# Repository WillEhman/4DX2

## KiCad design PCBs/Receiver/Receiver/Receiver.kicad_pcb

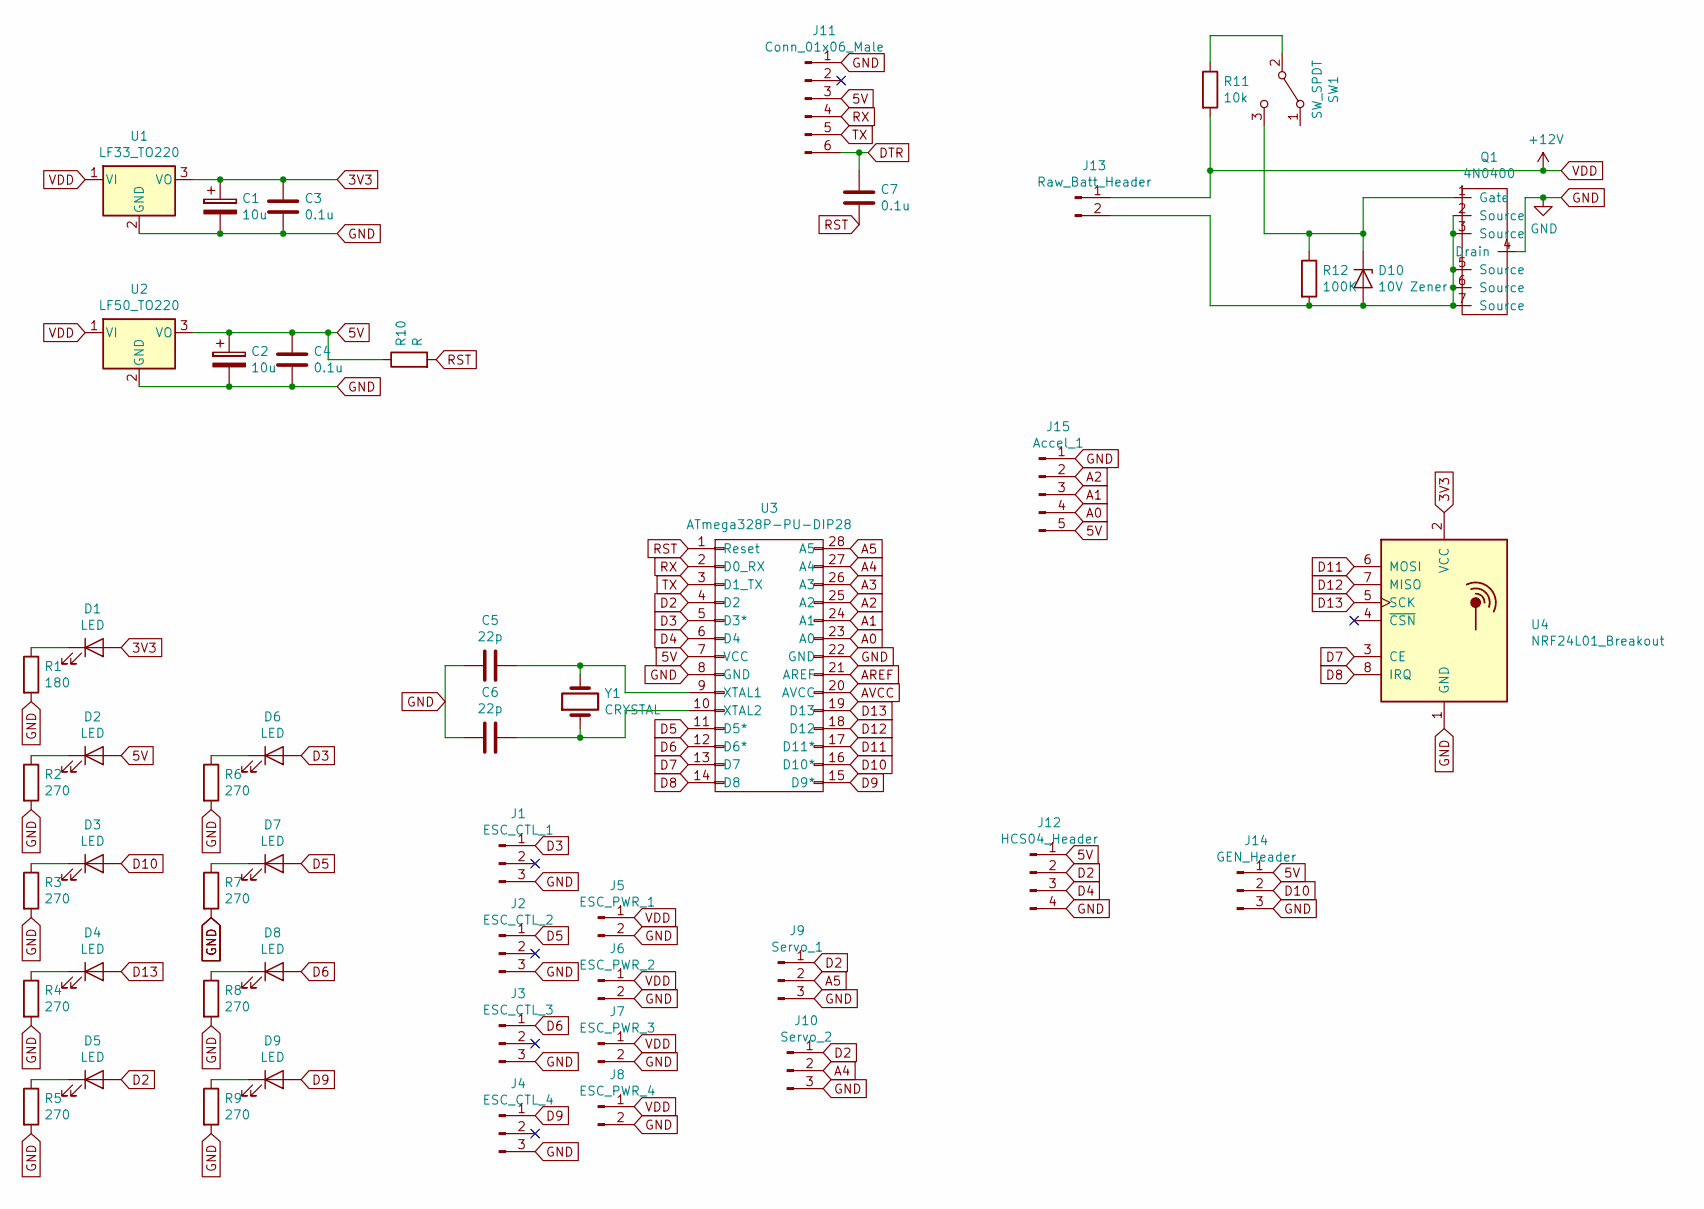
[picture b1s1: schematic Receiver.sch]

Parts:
C1, C2: 10u; CP_Radial_D5.0mm_P2.00mm
C3, C4, C7: 0.1u; C_Axial_L5.1mm_D3.1mm_P7.50mm_Horizontal
C5, C6: 22p; C_Axial_L3.8mm_D2.6mm_P7.50mm_Horizontal
D1, D2, D3, D4, D5, D6, D7, D8, D9: LED; LED_D3.0mm
D10: 10V Zener; D_DO-35_SOD27_P7.62mm_Horizontal
J1: ESC_CTL_1; PinHeader_1x03_P2.54mm_Horizontal
J2: ESC_CTL_2; PinHeader_1x03_P2.54mm_Horizontal
J3: ESC_CTL_3; PinHeader_1x03_P2.54mm_Horizontal
J4: ESC_CTL_4; PinHeader_1x03_P2.54mm_Horizontal
J5: ESC_PWR_1; SolderWirePad_1x02_P7.62mm_Drill2.5mm
J6: ESC_PWR_2; SolderWirePad_1x02_P7.62mm_Drill2.5mm
J7: ESC_PWR_3; SolderWirePad_1x02_P7.62mm_Drill2.5mm
J8: ESC_PWR_4; SolderWirePad_1x02_P7.62mm_Drill2.5mm
J9: Servo_1; PinHeader_1x03_P2.54mm_Vertical
J10: Servo_2; PinHeader_1x03_P2.54mm_Vertical
J11: Conn_01x06_Male; PinHeader_1x06_P2.54mm_Vertical
J12: HCS04_Header; PinSocket_1x04_P2.54mm_Vertical
J13: Raw_Batt_Header; SolderWirePad_1x02_P7.62mm_Drill2.5mm
J14: GEN_Header; PinSocket_1x03_P2.54mm_Vertical
J15: Accel_1; PinSocket_1x05_P2.54mm_Vertical
Q1: 4N0400; TO-263-7_TabPin4
R1: 180; R_Axial_DIN0207_L6.3mm_D2.5mm_P10.16mm_Horizontal
R2, R3, R4, R5, R6, R7, R8, R9: 270; R_Axial_DIN0207_L6.3mm_D2.5mm_P10.16mm_Horizontal
R10: R; R_Axial_DIN0207_L6.3mm_D2.5mm_P10.16mm_Horizontal
R11: 10k; R_Axial_DIN0207_L6.3mm_D2.5mm_P10.16mm_Horizontal
R12: 100K; R_Axial_DIN0207_L6.3mm_D2.5mm_P10.16mm_Horizontal
SW1: SW_SPDT; PinSocket_1x03_P2.54mm_Vertical
U1: LF33_TO220; TO-220-3_Vertical
U2: LF50_TO220; TO-220-3_Vertical
U3: ATmega328P-PU-DIP28; DIP-28_W7.62mm_Socket
U4: NRF24L01_Breakout; nRF24L01_Breakout
Y1: CRYSTAL; Crystal_HC49-U_Vertical

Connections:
3V3: C1.1, C3.1, D1.2 (A), U1.3 (VO), U4.2 (VCC)
5V: C2.1, C4.1, D2.2 (A), J11.3, J12.1, J14.1, J15.5, R10.1, U2.3 (VO), U3.7 (VCC)
A0: J15.4, U3.23 (A0)
A1: J15.3, U3.24 (A1)
A2: J15.2, U3.25 (A2)
A3: U3.26 (A3)
A4: J10.2, U3.27 (A4)
A5: J9.2, U3.28 (A5)
AREF: U3.21 (AREF)
AVCC: U3.20 (AVCC)
D2: D5.2 (A), J9.1, J10.1, J12.2, U3.4 (D2)
D3: D6.2 (A), J1.1, U3.5 (D3*)
D4: J12.3, U3.6 (D4)
D5: D7.2 (A), J2.1, U3.11 (D5*)
D6: D8.2 (A), J3.1, U3.12 (D6*)
D7: U3.13 (D7), U4.3 (CE)
D8: U3.14 (D8), U4.8 (IRQ)
D9: D9.2 (A), J4.1, U3.15 (D9*)
D10: D3.2 (A), J14.2, U3.16 (D10*)
D11: U3.17 (D11*), U4.6 (MOSI)
D12: U3.18 (D12), U4.7 (MISO)
D13: D4.2 (A), U3.19 (D13), U4.5 (SCK)
DTR: C7.1, J11.6
GND: C1.2, C2.2, C3.2, C4.2, C5.1, C6.1, J1.3, J2.3, J3.3, J4.3, J5.2, J6.2, J7.2, J8.2, J9.3, J10.3, J11.1, J12.4, J14.3, J15.1, Q1.4 (Drain), R1.2, R2.2, R3.2, R4.2, R5.2, R6.2, R7.2, R8.2, R9.2, U1.2 (GND), U2.2 (GND), U3.8 (GND), U3.22 (GND), U4.1 (GND)
unnamed: C5.2, U3.9 (XTAL1), Y1.2
unnamed: C6.2, U3.10 (XTAL2), Y1.1
unnamed: D1.1 (K), R1.1
unnamed: D2.1 (K), R2.1
unnamed: D3.1 (K), R3.1
unnamed: D4.1 (K), R4.1
unnamed: D5.1 (K), R5.1
unnamed: D6.1 (K), R6.1
unnamed: D7.1 (K), R7.1
unnamed: D8.1 (K), R8.1
unnamed: D9.1 (K), R9.1
unnamed: D10.1 (K), Q1.1 (Gate), R12.1, SW1.3 (C)
unnamed: D10.2 (A), J13.2, Q1.2 (Source), Q1.3 (Source), Q1.5 (Source), Q1.6 (Source), Q1.7 (Source), R12.2
unnamed: R11.1, SW1.2 (B)
RST: C7.2, R10.2, U3.1 (Reset)
RX: J11.4, U3.2 (D0_RX)
TX: J11.5, U3.3 (D1_TX)
VDD: J5.1, J6.1, J7.1, J8.1, J13.1, R11.2, U1.1 (VI), U2.1 (VI)

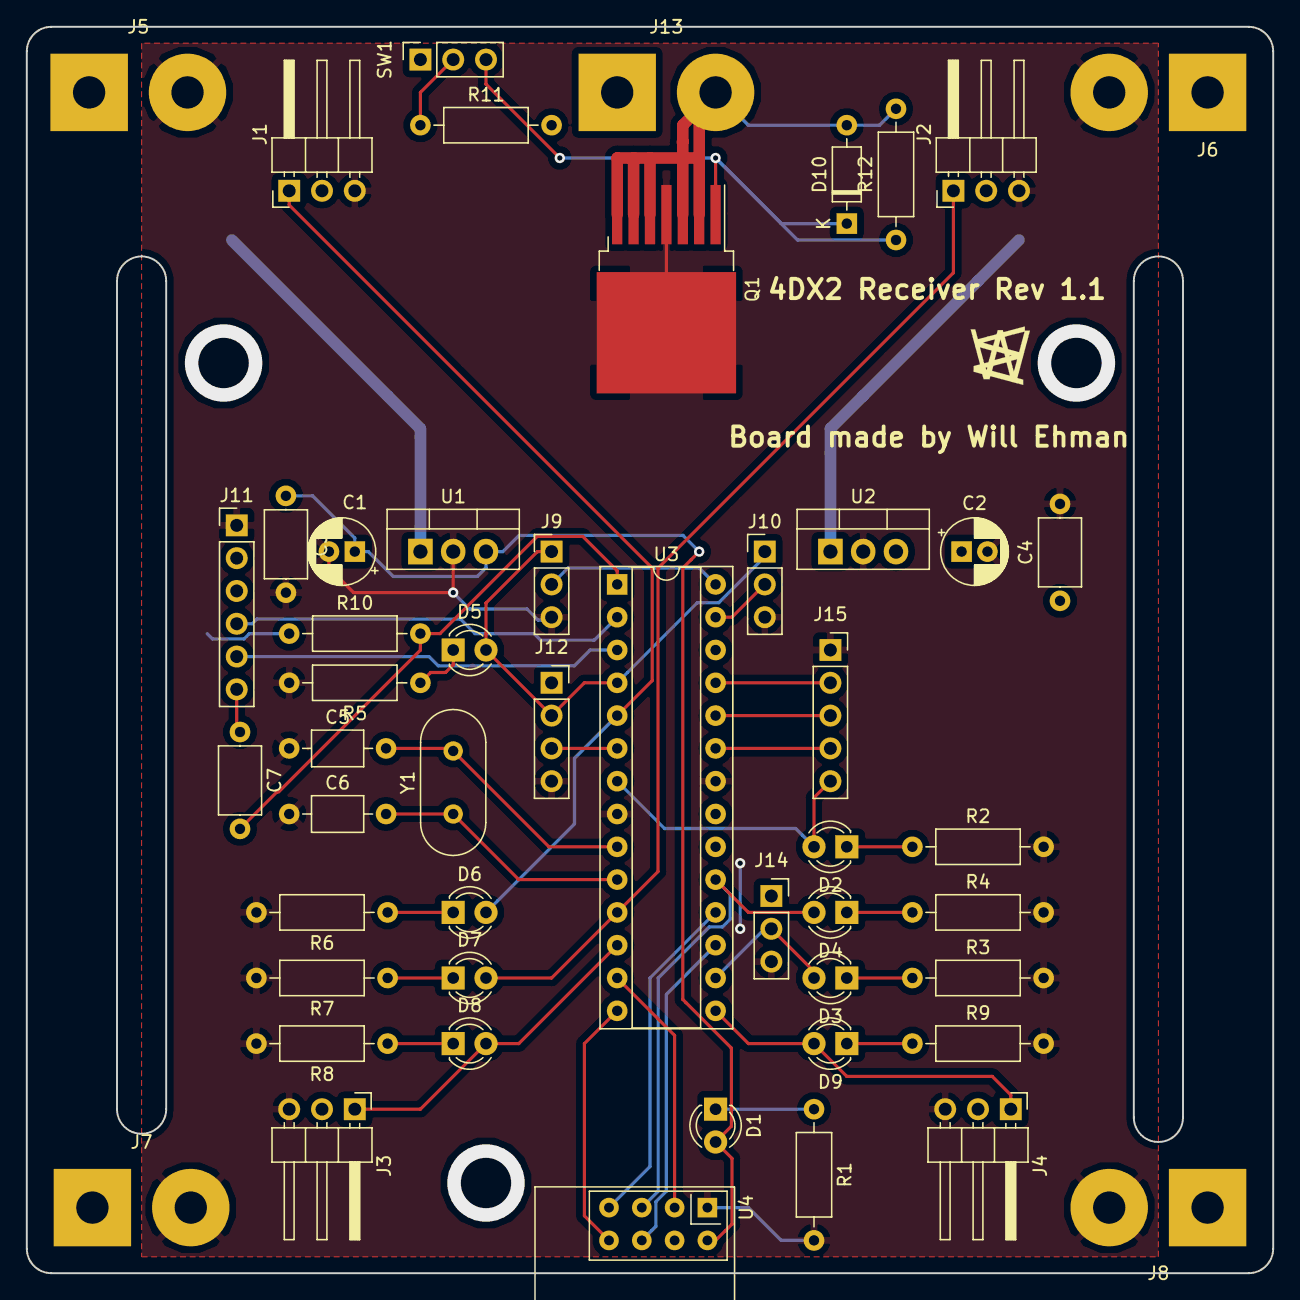
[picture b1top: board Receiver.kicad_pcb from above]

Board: 2 copper layers, 96.5 x 96.5 mm, 51 parts (0 on the bottom side), 39 nets.

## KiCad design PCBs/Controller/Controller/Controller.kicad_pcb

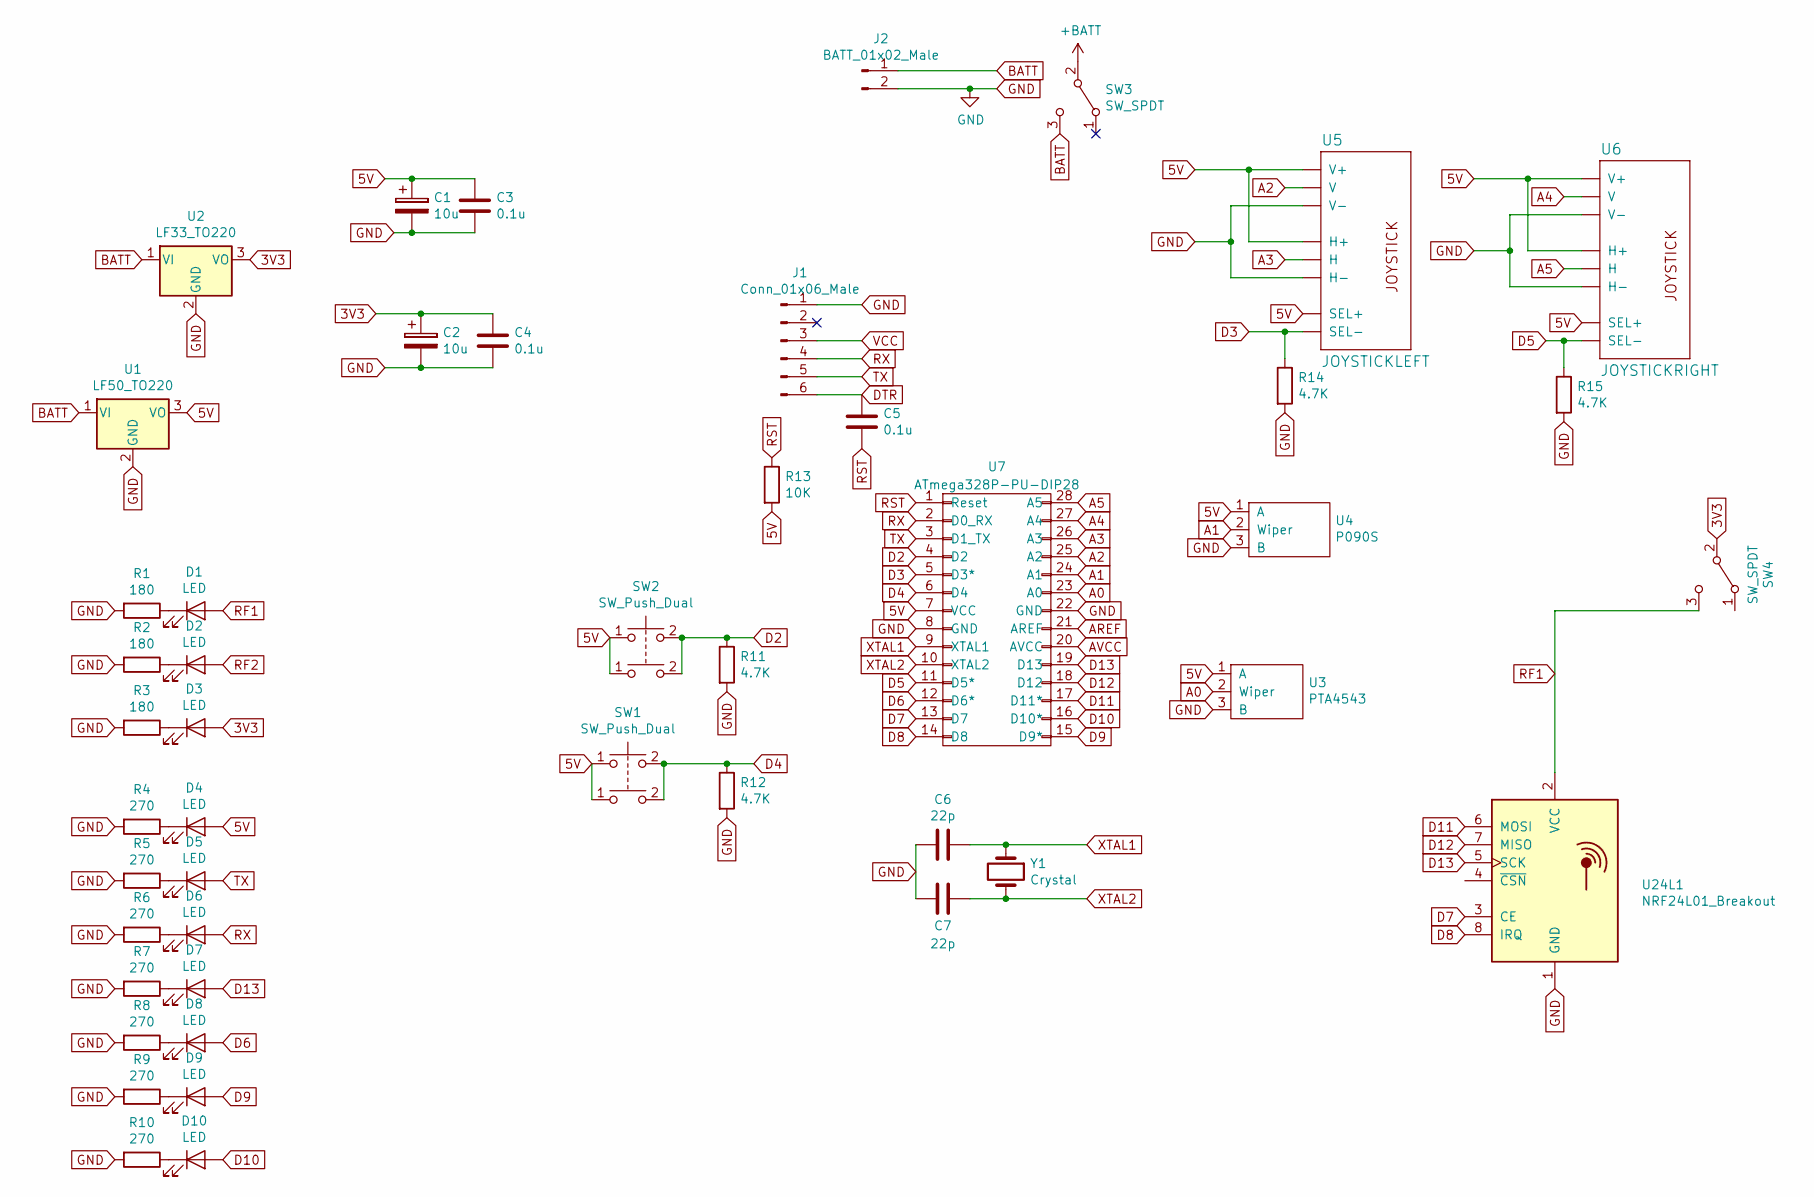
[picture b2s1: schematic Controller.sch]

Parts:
C1, C2: 10u; CP_Radial_D5.0mm_P2.00mm
C3, C4, C5: 0.1u; C_Axial_L5.1mm_D3.1mm_P7.50mm_Horizontal
C6, C7: 22p; C_Axial_L3.8mm_D2.6mm_P7.50mm_Horizontal
D1, D2, D3, D4, D5, D6, D7, D8, D9, D10: LED; LED_D3.0mm
J1: Conn_01x06_Male; PinHeader_1x06_P2.54mm_Vertical
J2: BATT_01x02_Male; PinHeader_1x02_P2.54mm_Vertical
R1, R2, R3: 180; R_Axial_DIN0207_L6.3mm_D2.5mm_P7.62mm_Horizontal
R4, R5, R6, R7, R8, R9, R10: 270; R_Axial_DIN0207_L6.3mm_D2.5mm_P7.62mm_Horizontal
R11, R12, R14, R15: 4.7K; R_Axial_DIN0207_L6.3mm_D2.5mm_P7.62mm_Horizontal
R13: 10K; R_Axial_DIN0207_L6.3mm_D2.5mm_P7.62mm_Horizontal
SW1, SW2: SW_Push_Dual; SW_PUSH_6mm_H5mm
SW3, SW4: SW_SPDT; PinHeader_1x03_P2.54mm_Vertical
U1: LF50_TO220; TO-220-3_Vertical
U2: LF33_TO220; TO-220-3_Vertical
U3: PTA4543; Potentiometer_Bourns_PTA4543_Single_Slide
U4: P090S; Potentiometer_Alps_RK09K_Single_Vertical
U5: JOYSTICKLEFT; JOYSTICK
U6: JOYSTICKRIGHT; JOYSTICK
U7: ATmega328P-PU-DIP28; DIP-28_W7.62mm
U24L1: NRF24L01_Breakout; nRF24L01_Breakout
Y1: Crystal; Crystal_HC49-U_Vertical

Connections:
3V3: C2.1, C4.1, D3.2 (A), SW4.2 (B), U2.3 (VO)
5V: C1.1, C3.1, D4.2 (A), R13.2, SW1.1, SW2.1, U1.3 (VO), U3.1 (A), U4.1 (A), U5.B1A (SEL+), U5.H1 (H+), U5.V1 (V+), U6.B1A (SEL+), U6.H1 (H+), U6.V1 (V+), U7.7 (VCC)
+BATT: SW3.2 (B)
A0: U3.2 (Wiper), U7.23 (A0)
A1: U4.2 (Wiper), U7.24 (A1)
A2: U5.V2 (V), U7.25 (A2)
A3: U5.H2 (H), U7.26 (A3)
A4: U6.V2 (V), U7.27 (A4)
A5: U6.H2 (H), U7.28 (A5)
AREF: U7.21 (AREF)
AVCC: U7.20 (AVCC)
BATT: J2.1, SW3.3 (C), U1.1 (VI), U2.1 (VI)
D2: R11.1, SW2.2, U7.4 (D2)
D3: R14.1, U5.B2A (SEL-), U7.5 (D3*)
D4: R12.1, SW1.2, U7.6 (D4)
D5: R15.1, U6.B2A (SEL-), U7.11 (D5*)
D6: D8.2 (A), U7.12 (D6*)
D7: U7.13 (D7), U24L1.3 (CE)
D8: U7.14 (D8), U24L1.8 (IRQ)
D9: D9.2 (A), U7.15 (D9*)
D10: D10.2 (A), U7.16 (D10*)
D11: U7.17 (D11*), U24L1.6 (MOSI)
D12: U7.18 (D12), U24L1.7 (MISO)
D13: D7.2 (A), U7.19 (D13), U24L1.5 (SCK)
DTR: C5.1, J1.6
GND: C1.2, C2.2, C3.2, C4.2, C6.2, C7.2, J1.1, J2.2, R1.2, R2.2, R3.2, R4.2, R5.2, R6.2, R7.2, R8.2, R9.2, R10.2, R11.2, R12.2, R14.2, R15.2, U1.2 (GND), U2.2 (GND), U3.3 (B), U4.3 (B), U5.H3 (H-), U5.V3 (V-), U6.H3 (H-), U6.V3 (V-), U7.8 (GND), U7.22 (GND), U24L1.1 (GND)
unnamed: D1.1 (K), R1.1
unnamed: D2.1 (K), R2.1
unnamed: D3.1 (K), R3.1
unnamed: D4.1 (K), R4.1
unnamed: D5.1 (K), R5.1
unnamed: D6.1 (K), R6.1
unnamed: D7.1 (K), R7.1
unnamed: D8.1 (K), R8.1
unnamed: D9.1 (K), R9.1
unnamed: D10.1 (K), R10.1
RF1: D1.2 (A), SW4.3 (C), U24L1.2 (VCC)
RF2: D2.2 (A)
RST: C5.2, R13.1, U7.1 (Reset)
RX: D6.2 (A), J1.4, U7.2 (D0_RX)
TX: D5.2 (A), J1.5, U7.3 (D1_TX)
VCC: J1.3
XTAL1: C6.1, U7.9 (XTAL1), Y1.1
XTAL2: C7.1, U7.10 (XTAL2), Y1.2

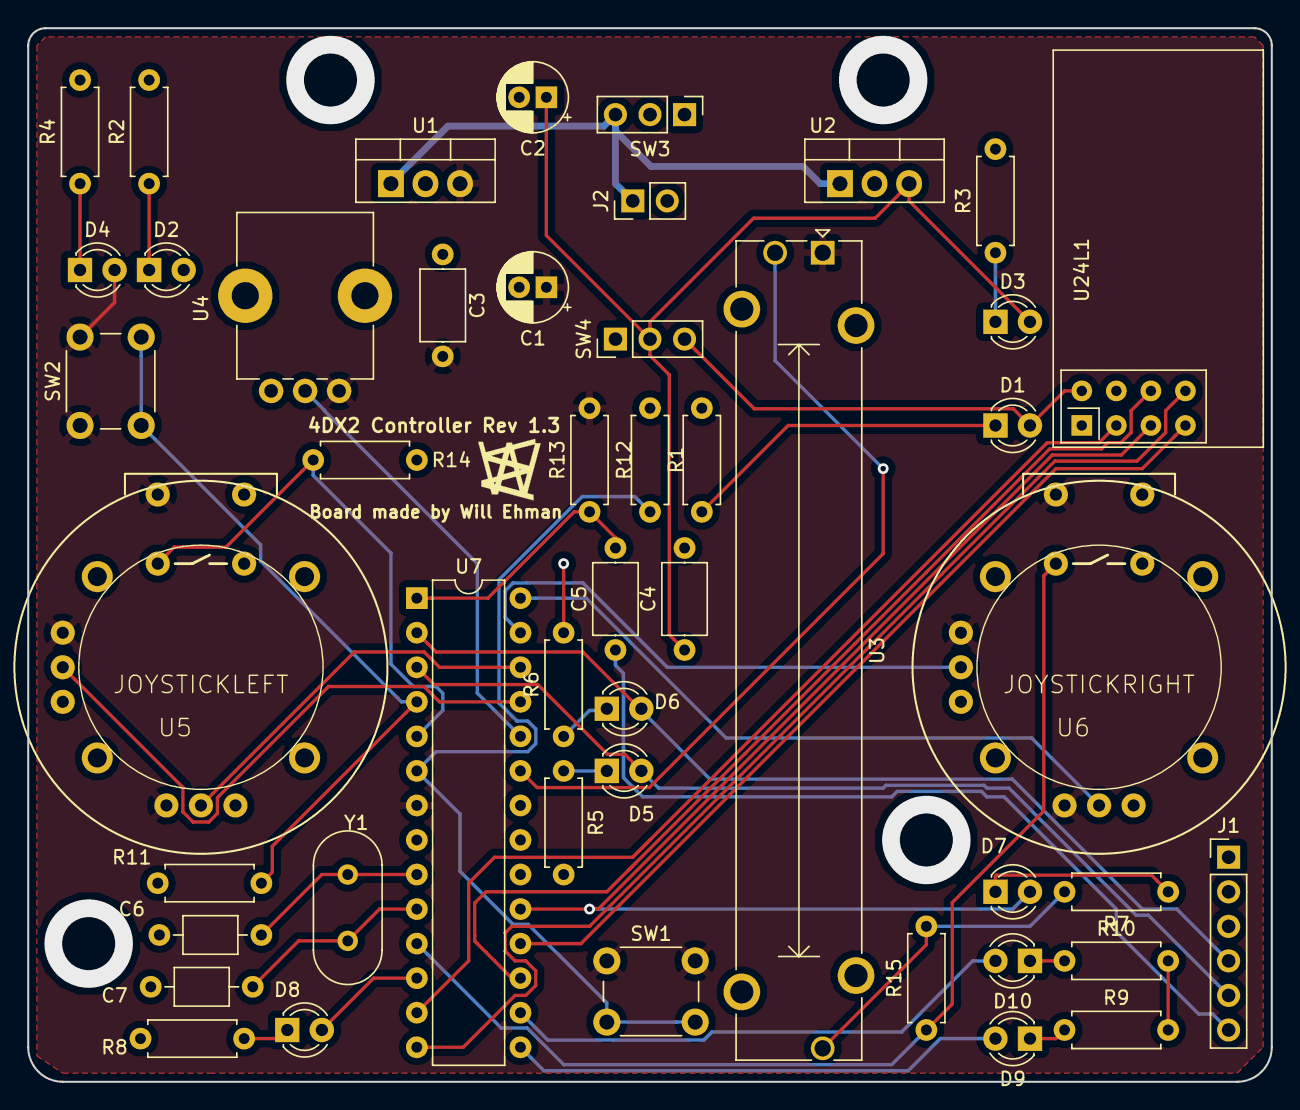
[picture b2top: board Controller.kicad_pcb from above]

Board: 2 copper layers, 91.4 x 77.5 mm, 47 parts (0 on the bottom side), 39 nets.

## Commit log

2019-01-29 initial push for pcb files
2019-01-29 Developed Controller Schematic v1
2019-01-29 Properly replaced Joystick schematic
    all footprints should be good
    Solution was found at path
    https://github.com/benwis/SparkFun-Kicad-Libraries/blob/master/SparkFun-Electromechanical.pretty/JOYSTICK.kicad_mod
2019-01-29 Footprints and netlist generated without errors - ready for pcb development
2019-01-30 Finsihed PCB Layout - exported Gerbers v1
2019-01-30 Exported PDFs
2019-02-13 Reduced complexity, removed 1 rf module
2019-02-14 Generating Gerber Files for 2.0 board rev (Sent for manufacturing)
2019-02-14 Developed Receiver Schematic and PCB for 1.0
    Identified issue with Controller programming header VCC not properly connected to 5V - Can be fixed with jumper in production - rev 1.3 made
2019-02-17 Rev 1.1 of Receiver Board - added mounts and cutouts for seperation
2019-02-17 Aesthetic Updates to prep for manu
